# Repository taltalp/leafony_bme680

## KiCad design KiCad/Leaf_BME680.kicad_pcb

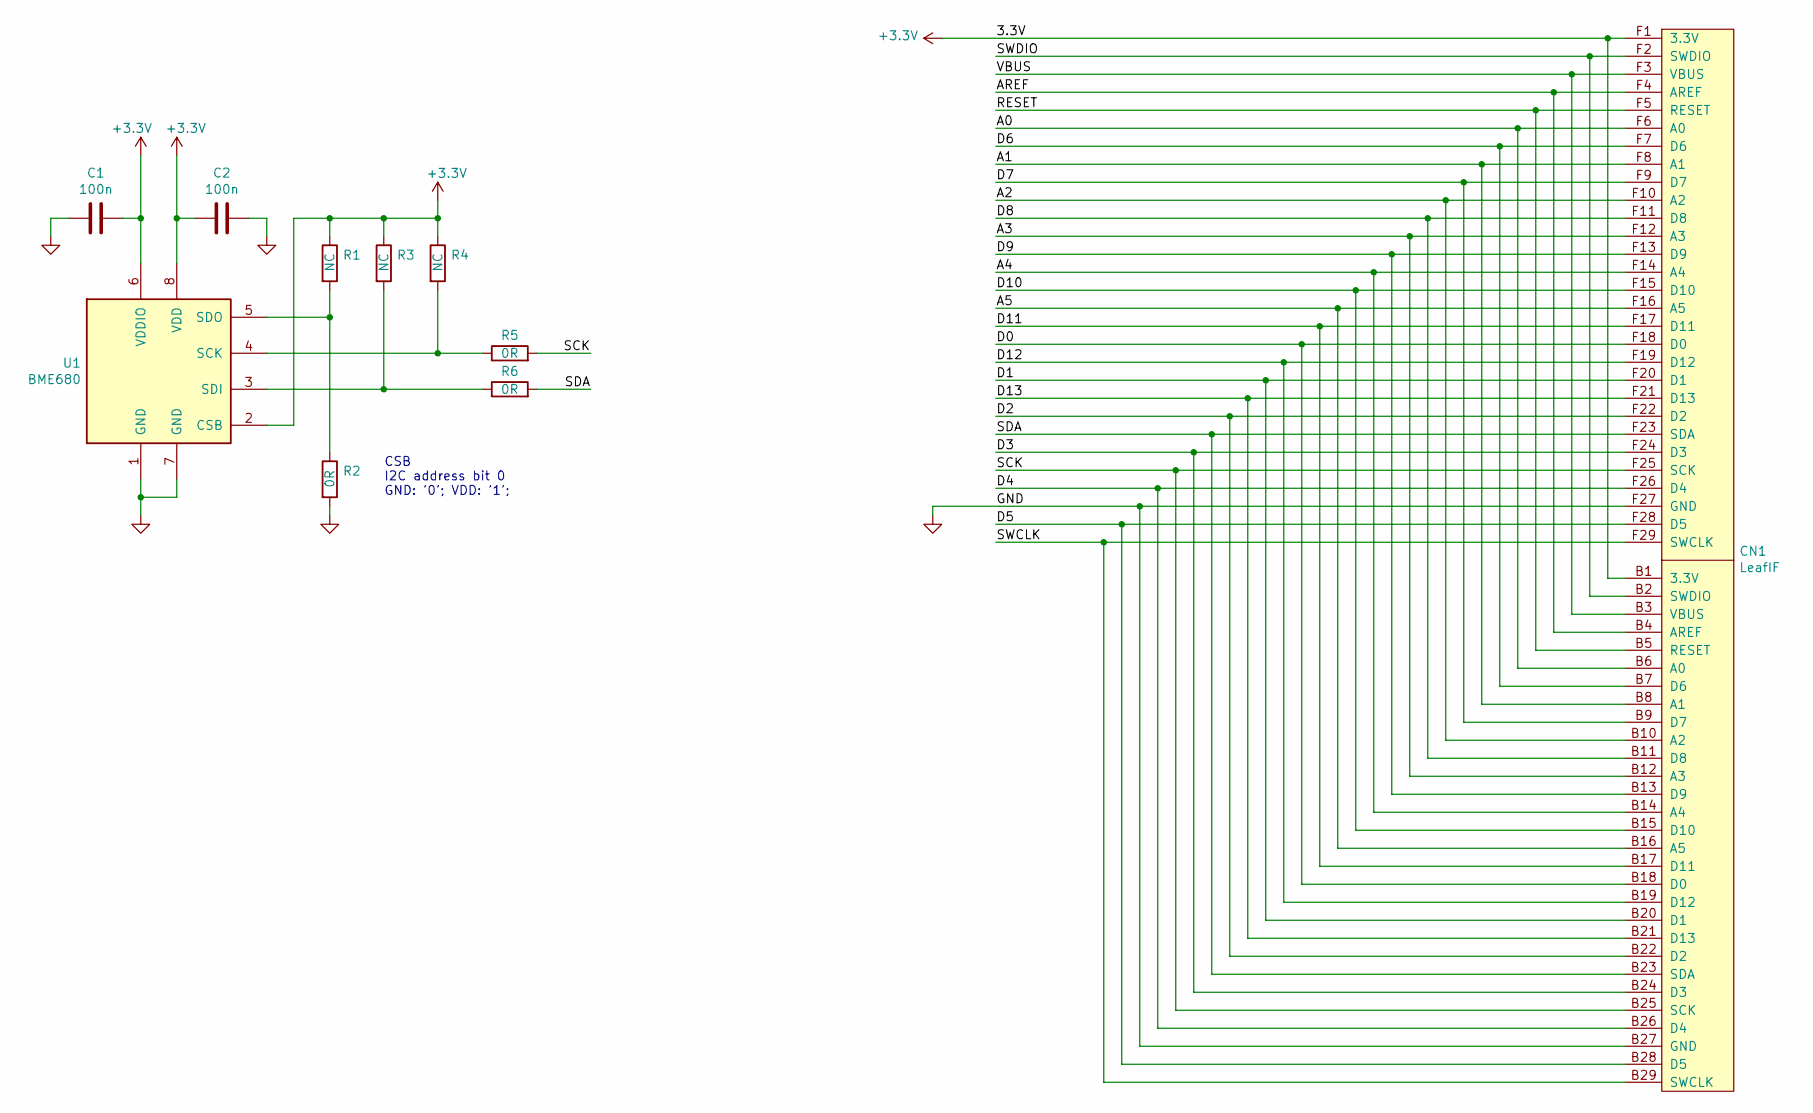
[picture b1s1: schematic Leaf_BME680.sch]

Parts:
C1, C2: 100n; C_0603_1608Metric
CN1: LeafIF; CN_F29_B29
R1, R3, R4: NC; R_0603_1608Metric
R2, R5, R6: 0R; R_0603_1608Metric
U1: BME680; Bosch_LGA-8_3x3mm_P0.8mm_ClockwisePinNumbering

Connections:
+3V3: C1.1, C2.2, CN1.B1 (3.3V), CN1.F1 (3.3V), R1.1, R3.1, R4.1, U1.2 (CSB), U1.6 (VDDIO), U1.8 (VDD)
/A0: CN1.B6 (A0), CN1.F6 (A0)
/A1: CN1.B8 (A1), CN1.F8 (A1)
/A2: CN1.B10 (A2), CN1.F10 (A2)
/A3: CN1.B12 (A3), CN1.F12 (A3)
/A4: CN1.B14 (A4), CN1.F14 (A4)
/A5: CN1.B16 (A5), CN1.F16 (A5)
/AREF: CN1.B4 (AREF), CN1.F4 (AREF)
/D0: CN1.B18 (D0), CN1.F18 (D0)
/D1: CN1.B20 (D1), CN1.F20 (D1)
/D2: CN1.B22 (D2), CN1.F22 (D2)
/D3: CN1.B24 (D3), CN1.F24 (D3)
/D4: CN1.B26 (D4), CN1.F26 (D4)
/D5: CN1.B28 (D5), CN1.F28 (D5)
/D6: CN1.B7 (D6), CN1.F7 (D6)
/D7: CN1.B9 (D7), CN1.F9 (D7)
/D8: CN1.B11 (D8), CN1.F11 (D8)
/D9: CN1.B13 (D9), CN1.F13 (D9)
/D10: CN1.B15 (D10), CN1.F15 (D10)
/D11: CN1.B17 (D11), CN1.F17 (D11)
/D12: CN1.B19 (D12), CN1.F19 (D12)
/D13: CN1.B21 (D13), CN1.F21 (D13)
/RESET: CN1.B5 (RESET), CN1.F5 (RESET)
/SCK: CN1.B25 (SCK), CN1.F25 (SCK), R5.2
/SDA: CN1.B23 (SDA), CN1.F23 (SDA), R6.2
/SWCLK: CN1.B29 (SWCLK), CN1.F29 (SWCLK)
/SWDIO: CN1.B2 (SWDIO), CN1.F2 (SWDIO)
/VBUS: CN1.B3 (VBUS), CN1.F3 (VBUS)
GND: C1.2, C2.1, CN1.B27 (GND), CN1.F27 (GND), R2.2, U1.1 (GND), U1.7 (GND)
unnamed: R1.2, R2.1, U1.5 (SDO)
unnamed: R3.2, R6.1, U1.3 (SDI)
unnamed: R4.2, R5.1, U1.4 (SCK)

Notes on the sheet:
CSB I2C address bit 0 GND: '0'; VDD: '1';

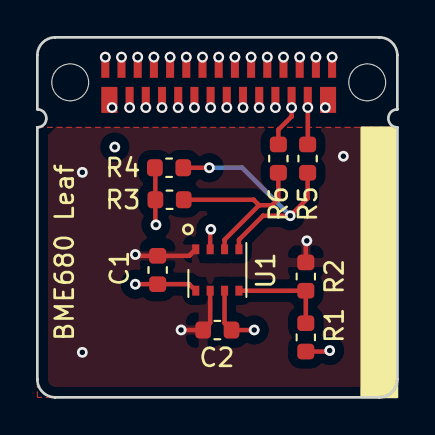
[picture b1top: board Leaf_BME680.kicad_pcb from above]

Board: 4 copper layers, 20.0 x 20.0 mm, 10 parts (0 on the bottom side), 32 nets.

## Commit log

2020-01-03 add spreadsheet-logger
2020-07-19 update pcb
2020-09-02 Bump bl from 3.0.0 to 3.0.1 in /spreadsheet-logger
    Bumps [bl](https://github.com/rvagg/bl) from 3.0.0 to 3.0.1.
    - [Release notes](https://github.com/rvagg/bl/releases)
    - [Commits](https://github.com/rvagg/bl/compare/v3.0.0...v3.0.1)
2020-09-12 Bump node-fetch from 2.6.0 to 2.6.1 in /spreadsheet-logger
    Bumps [node-fetch](https://github.com/bitinn/node-fetch) from 2.6.0 to 2.6.1.
    - [Release notes](https://github.com/bitinn/node-fetch/releases)
    - [Changelog](https://github.com/node-fetch/node-fetch/blob/master/docs/CHANGELOG.md)
    - [Commits](https://github.com/bitinn/node-fetch/compare/v2.6.0...v2.6.1)
2020-12-12 Bump ini from 1.3.5 to 1.3.8 in /spreadsheet-logger
    Bumps [ini](https://github.com/isaacs/ini) from 1.3.5 to 1.3.8.
    - [Release notes](https://github.com/isaacs/ini/releases)
    - [Commits](https://github.com/isaacs/ini/compare/v1.3.5...v1.3.8)
2021-08-04 Bump tar from 4.4.13 to 4.4.15 in /spreadsheet-logger
    Bumps [tar](https://github.com/npm/node-tar) from 4.4.13 to 4.4.15.
    - [Release notes](https://github.com/npm/node-tar/releases)
    - [Changelog](https://github.com/npm/node-tar/blob/main/CHANGELOG.md)
    - [Commits](https://github.com/npm/node-tar/compare/v4.4.13...v4.4.15)
    ---
    updated-dependencies:
2021-09-02 Bump tar from 4.4.13 to 4.4.19 in /spreadsheet-logger
    Bumps [tar](https://github.com/npm/node-tar) from 4.4.13 to 4.4.19.
    - [Release notes](https://github.com/npm/node-tar/releases)
    - [Changelog](https://github.com/npm/node-tar/blob/main/CHANGELOG.md)
    - [Commits](https://github.com/npm/node-tar/compare/v4.4.13...v4.4.19)
    ---
    updated-dependencies:
2022-01-22 Bump node-fetch from 2.6.0 to 2.6.7 in /spreadsheet-logger
    Bumps [node-fetch](https://github.com/node-fetch/node-fetch) from 2.6.0 to 2.6.7.
    - [Release notes](https://github.com/node-fetch/node-fetch/releases)
    - [Changelog](https://github.com/node-fetch/node-fetch/blob/main/docs/CHANGELOG.md)
    - [Commits](https://github.com/node-fetch/node-fetch/compare/v2.6.0...v2.6.7)
    ---
    updated-dependencies:
2022-12-06 Bump qs from 6.9.0 to 6.11.0 in /spreadsheet-logger
    Bumps [qs](https://github.com/ljharb/qs) from 6.9.0 to 6.11.0.
    - [Release notes](https://github.com/ljharb/qs/releases)
    - [Changelog](https://github.com/ljharb/qs/blob/main/CHANGELOG.md)
    - [Commits](https://github.com/ljharb/qs/compare/v6.9.0...v6.11.0)
    ---
    updated-dependencies:
